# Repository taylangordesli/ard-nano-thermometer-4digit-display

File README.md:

# ard-nano-thermometer-4digit-display
An entrance level thermometer project for PCB design that includes Arduino Nano as a microcontroller, LM35 sensor,  4 digit 7 segment display and if needed, there is a LM7805 voltage regulator with 5V output if there is a need to use I added a connector which can supply max 2 device.

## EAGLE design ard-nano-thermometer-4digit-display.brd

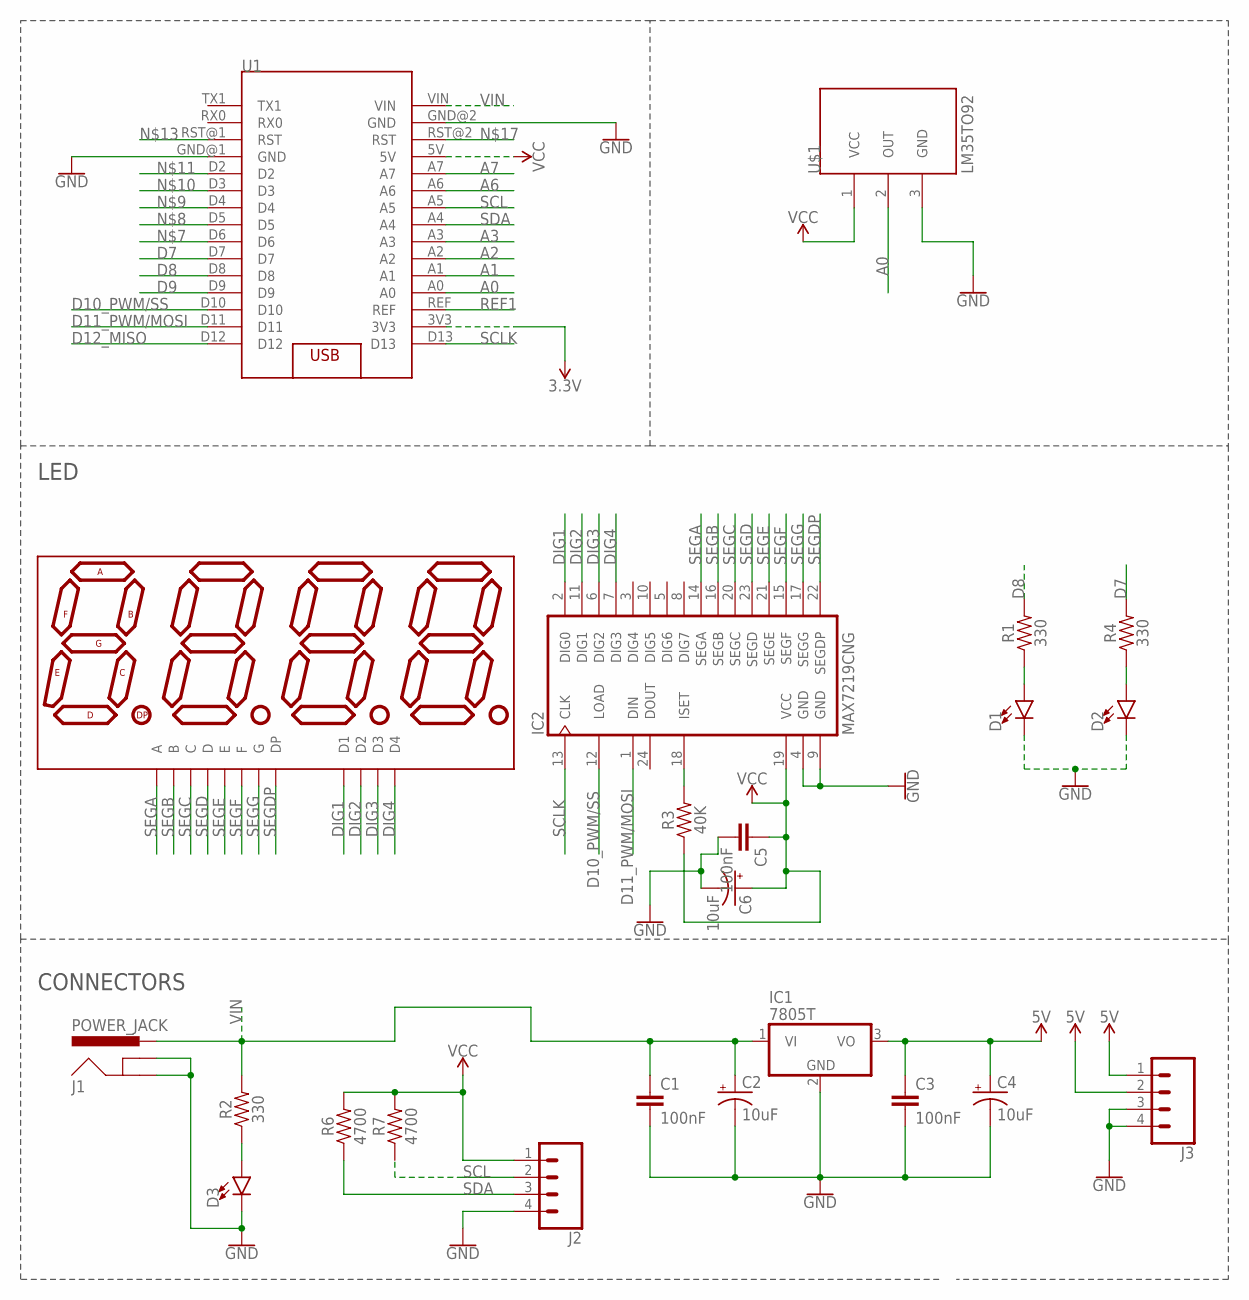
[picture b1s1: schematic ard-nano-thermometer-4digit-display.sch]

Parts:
C1, C3, C5: 100nF; CAP-PTH-10MM
C2, C4, C6: 10uF; CPOL-RADIAL-2.5MM-5MM
D1, D2, D3: LED3MM; LED_3MM
DISP1: ATA8041AB; 7-SEGMENT-4DIGIT-20MM
IC1: 7805T; TO220H
IC2: MAX7219CNG; DIL24-3
J1: POWER_JACK; POWER_JACK_PTH
J2, J3: CONN_04PTH; 1X04
R1, R2, R4: 330; AXIAL-0.3
R3: 40K; AXIAL-0.3
R6, R7: 4700; AXIAL-0.3
U1: ARDUINO_NANO
U$1: LM35TO92

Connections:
3.3V: U1.3V3
5V: C3.1, C4.1 (+), IC1.3 (VO), J3.1, J3.2
A0: U1.A0, U$1.2 (OUT)
A1: U1.A1
A2: U1.A2
A3: U1.A3
A6: U1.A6
A7: U1.A7
D7: R4.P$2 (2), U1.D7
D8: R1.P$2 (2), U1.D8
D9: U1.D9
D10_PWM/SS: IC2.12 (LOAD), U1.D10
D11_PWM/MOSI: IC2.1 (DIN), U1.D11
D12_MISO: U1.D12
DIG1: DISP1.12 (D1), IC2.2 (DIG0)
DIG2: DISP1.9 (D2), IC2.11 (DIG1)
DIG3: DISP1.8 (D3), IC2.6 (DIG2)
DIG4: DISP1.6 (D4), IC2.7 (DIG3)
GND: C1.2, C2.2 (-), C3.2, C4.2 (-), C5.2, C6.2 (-), D1.K (C), D2.K (C), D3.K (C), IC1.2 (GND), IC2.4 (GND), IC2.9 (GND), J1.GND, J1.GNDBREAK, J2.4, J3.3, J3.4, U1.GND@1 (GND), U1.GND@2 (GND), U$1.3 (GND)
unnamed: D3.A, R2.P$1 (1)
unnamed: D1.A, R1.P$1 (1)
unnamed: D2.A, R4.P$1 (1)
unnamed: IC2.18 (ISET), R3.P$2 (2)
REF1: U1.REF
SCL: J2.2, R7.P$1 (1), U1.A5
SCLK: IC2.13 (CLK), U1.D13
SDA: J2.3, R6.P$1 (1), U1.A4
SEGA: DISP1.11 (A), IC2.14 (SEGA)
SEGB: DISP1.7 (B), IC2.16 (SEGB)
SEGC: DISP1.4 (C), IC2.20 (SEGC)
SEGD: DISP1.2 (D), IC2.23 (SEGD)
SEGDP: DISP1.3 (DP), IC2.22 (SEGDP)
SEGE: DISP1.1 (E), IC2.21 (SEGE)
SEGF: DISP1.10 (F), IC2.15 (SEGF)
SEGG: DISP1.5 (G), IC2.17 (SEGG)
VCC: C5.1, C6.1 (+), IC2.19 (VCC), J2.1, R3.P$1 (1), R6.P$2 (2), R7.P$2 (2), U1.5V, U$1.1 (VCC)
VIN: C1.1, C2.1 (+), IC1.1 (VI), J1.PWR, R2.P$2 (2), U1.VIN

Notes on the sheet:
CONNECTORS
LED

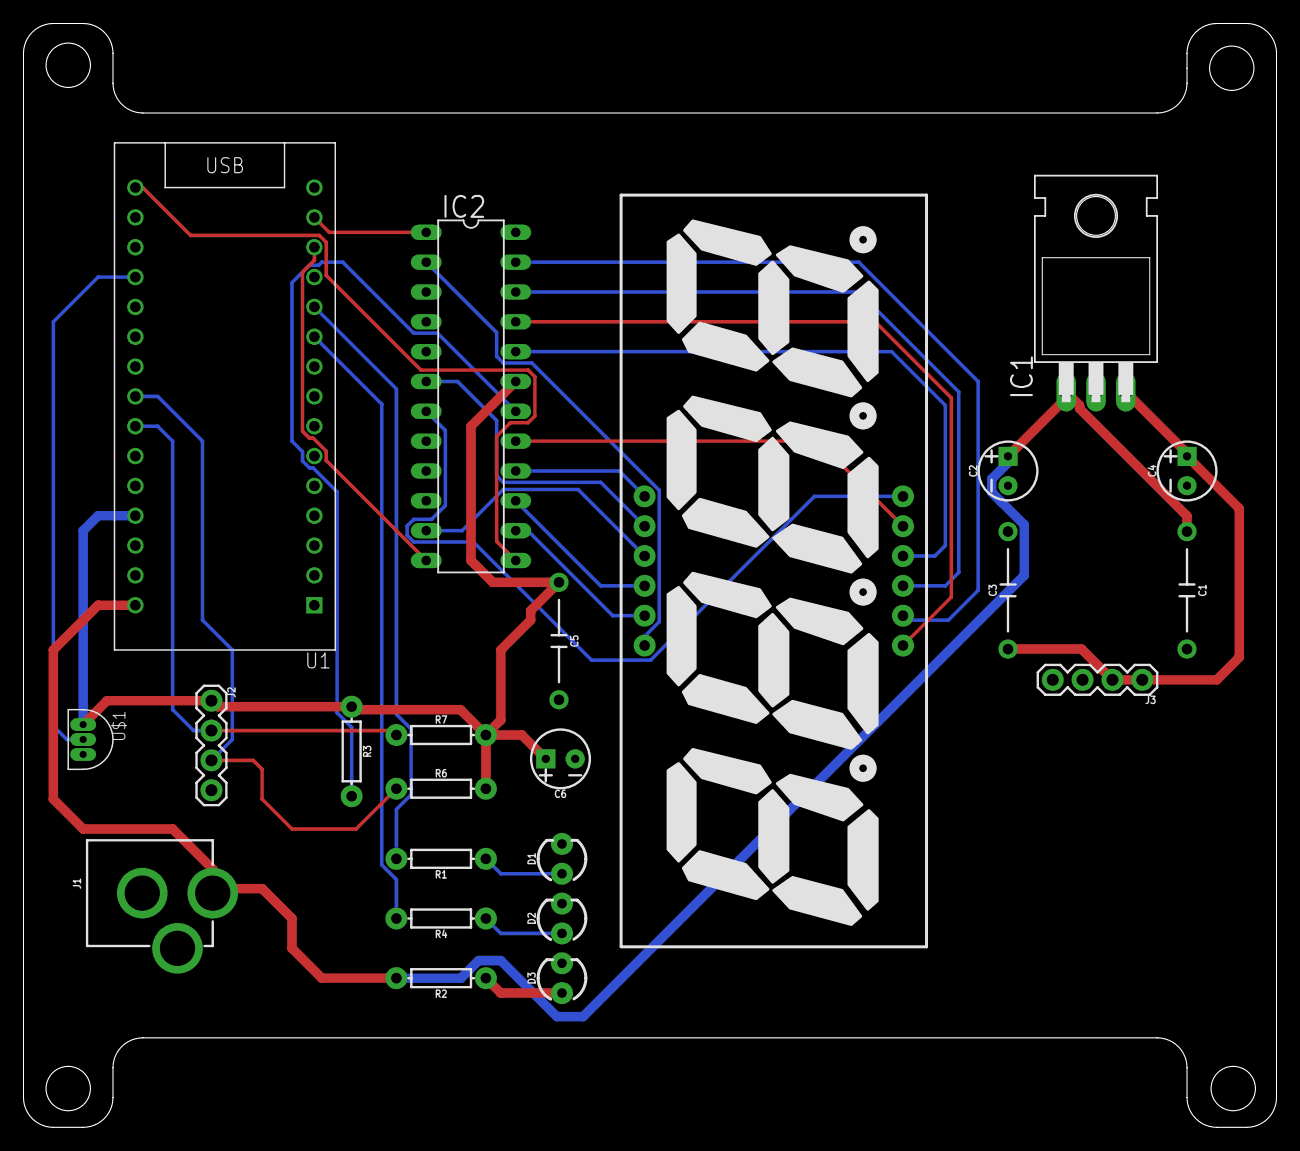
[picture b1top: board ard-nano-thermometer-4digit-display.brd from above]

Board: 2 copper layers, 106.7 x 94.0 mm, 23 parts (0 on the bottom side), 28 nets.

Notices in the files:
parts and their libraries:
SparkFun-Capacitors: Licensing: Creative Commons ShareAlike 4.0 International - https://creativecommons.org/licenses/by-sa/4.0
